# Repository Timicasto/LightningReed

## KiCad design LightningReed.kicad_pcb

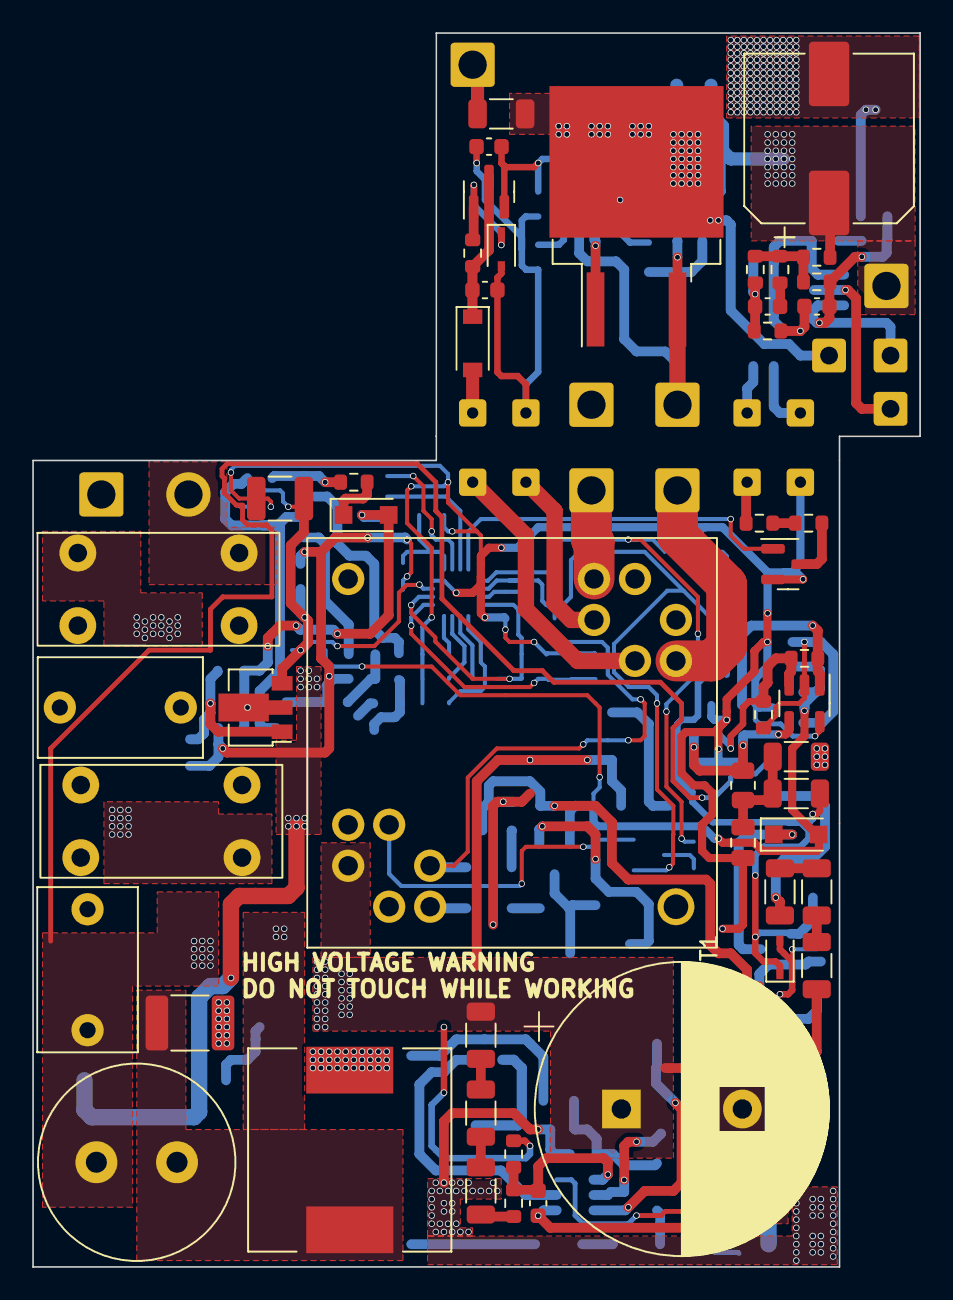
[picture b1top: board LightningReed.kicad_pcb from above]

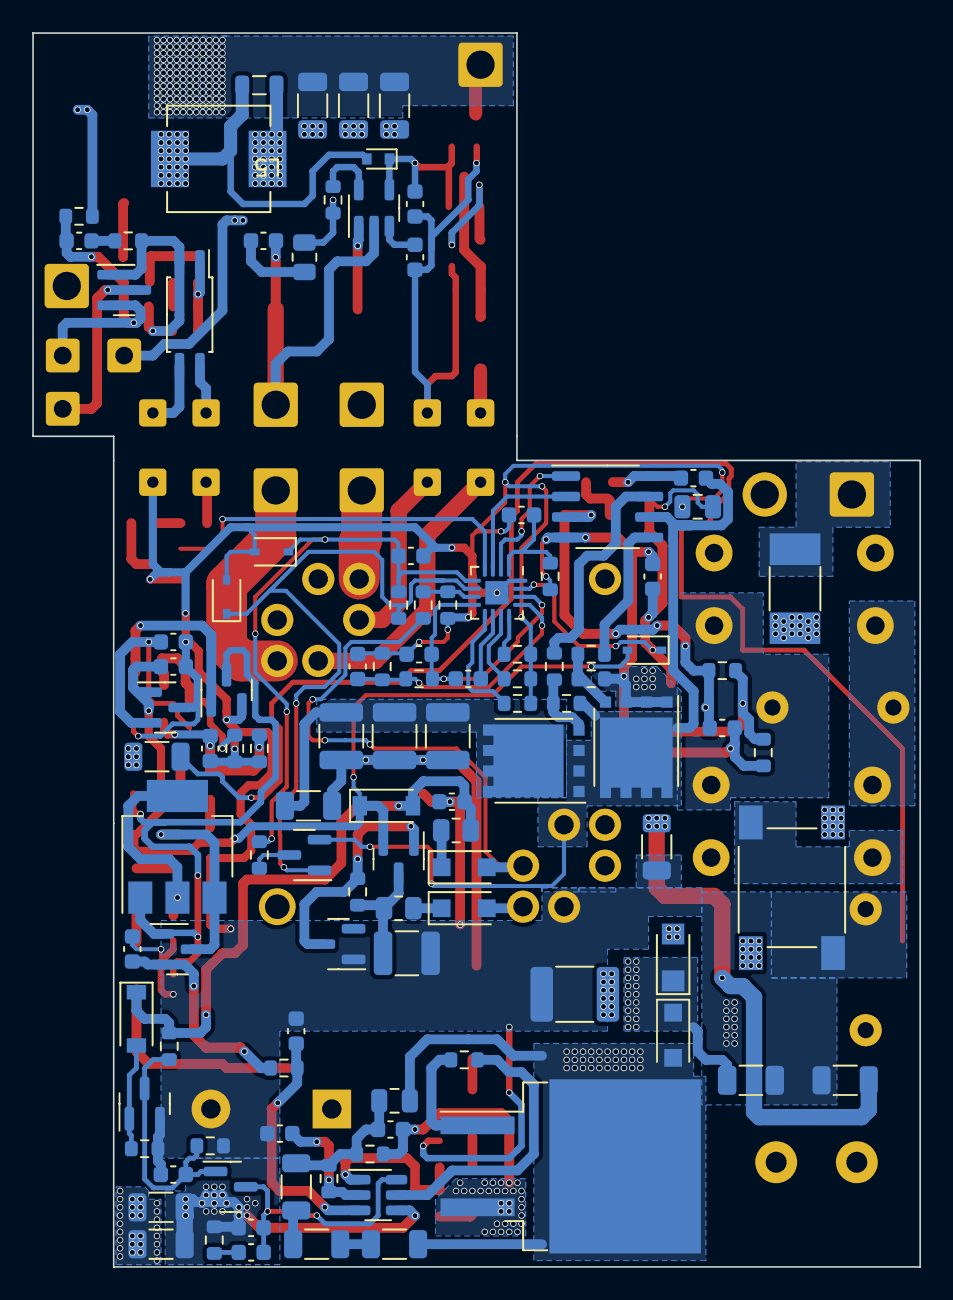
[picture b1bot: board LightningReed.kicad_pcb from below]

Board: 2 copper layers, 55.0 x 76.5 mm, 175 parts (108 on the bottom side), 102 nets.

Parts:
C1: 470nF; C_Rect_L10.0mm_W6.0mm_P7.50mm_MKS4
C2: 220nF; C_Rect_L10.0mm_W6.0mm_P7.50mm_MKS4
C3, C19: 470nF; C_1812_4532Metric
C4: 10pF; C_0805_2012Metric
C5: 3900pF; C_0603_1608Metric
C6, C11, C12, C13, C15, C25, C44, C45, C46: 1uF; C_0603_1608Metric
C7: 33nF; C_0603_1608Metric
C8, C14, C17, C31, C32, C38: 220pF; C_0603_1608Metric
C9: 2200pF; C_0603_1608Metric
C10: 68uF; CP_Radial_D18.0mm_P7.50mm
C16: 100nF; C_0805_2012Metric
C18: 100nF; C_1206_3216Metric
C20, C21, C22: 330nF; C_1210_3225Metric
C23: 47nF; C_0603_1608Metric
C24, C30: 100nF; C_0603_1608Metric
C26, C47: 2.2uF; C_0603_1608Metric
C27: 4.7uF; C_1210_3225Metric
C28: 4.7uF; C_0805_2012Metric
C29: 22uF; C_1210_3225Metric
C33: 33pF; C_0603_1608Metric
C34: 22pF; C_0603_1608Metric
C35: 4.7nF; C_0603_1608Metric
C36: 10nF; C_0603_1608Metric
C37: 3.3pF; C_0603_1608Metric
C39, C40, C41, C42: 33uF; C_1206_3216Metric
C43: 680uF; CP_Elec_10x10
D1: ES3JF; D_SMF
D2: MSB40M; UMSB
D3: ES2JW; D_SOD-123F
D4: BZT52C16S; D_SOD-323
D5: DSK16; D_SOD-123F
D6: BZT52C13; D_SOD-123
D7: U1J; D_SOD-123F
D8, D9: ES1JW; D_SOD-123F
D10: SD103AW; D_SOD-123
D11: BAS70WS; D_SOD-323
D12: BZX84C16; SOT-23
D13: MM3Z20; D_SOD-323
D14: MM3Z24; D_SOD-323
D15: RF081M2STR; D_SOD-123
D16: MM3Z10; D_SOD-323
D17: RFU02VSM8S; D_SOD-523
F1: JFC2410-1500TS; JFC2410
L1, L2: 5mH; CHOKE
L3: SDA0912-150uH-0.45; L_Radial_D12.0mm_P5.00mm_Fastron_11P
L4: 7447709471; L_12x12mm_H8mm
L5: 1uH; CKST0603
L6: 680nH; L_0805_2012Metric
P1: Conn_WallPlug; SolderWire-1sqmm_1x02_P5.4mm_D1.4mm_OD2.7mm
Q1: NCE65T180D; TO-263-2
Q2, Q4: 2N7002; SOT-23
Q3: 1N60G; SOT-223-3_TabPin2
Q5, Q6, Q11: 2N7002K; SOT-23
Q7, Q8: CMSA65R280Q; VSONP-8-1EP_5x6_P1.27mm
Q9: NCE0102; SOT-23
Q10: DMZ6005E; SOT-23
Q12: NCEP15T14D; TO-263-2
Q13: BSS123; SOT-23
R1, R31, R35, R54: 10; R_0603_1608Metric
R2, R3, R4, R10, R11, R12, R19, R20, R24: 3M24; R_1206_3216Metric
R5: 24K3; R_0603_1608Metric
R6, R7, R38, R39: 220m; R_1206_3216Metric
R8: 182K; R_0603_1608Metric
R9: 750; R_0603_1608Metric
R13, R44: 274K; R_0603_1608Metric
R14: 64k9; R_0603_1608Metric
R15: 2; R_0603_1608Metric
R16, R18, R28: 100K; R_0603_1608Metric
R17: 39K2; R_0603_1608Metric
R21, R22, R23: 1K; R_1206_3216Metric
R25: 3M16; R_0805_2012Metric
R26: 178K; R_0603_1608Metric
R27: 49K9; R_0603_1608Metric
R29, R32, R34, R56: 10K; R_0603_1608Metric
R30: 2M21; R_1206_3216Metric
R33: 24.9; R_0603_1608Metric
R36: 470; R_0603_1608Metric
R37: 3K24; R_0603_1608Metric
R40, R41: 1; R_0805_2012Metric
R42, R43, R58, R60: 150K; R_0603_1608Metric
R45, R46: 332K; R_0603_1608Metric
R47: 1K21; R_0603_1608Metric
R48: 1M; R_0603_1608Metric
R49: 121; R_0603_1608Metric
R50: 12K4; R_0603_1608Metric
R51, R63: 75K; R_0603_1608Metric
R52: 30K1; R_0603_1608Metric
R53: 432K; R_0603_1608Metric
R55: 562; R_0603_1608Metric
R57: 15K; R_0603_1608Metric
R59: 56K2; R_0603_1608Metric
R61: 22; R_0805_2012Metric
R62: 100; R_0603_1608Metric
T1: Transformer_2P_2S; RM10
TH1: 100K; R_0603_1608Metric
TP1: TestPoint_Alt; SolderWire-1sqmm_1x01_D1.4mm_OD2.7mm
TP2, TP3, TP4: TestPoint_Alt; SolderWire-0.5sqmm_1x01_D0.9mm_OD2.1mm
TP5, TP6, TP7, TP8: TestPoint; SolderWire-1sqmm_1x01_D1.4mm_OD2.7mm
TP9, TP10, TP11, TP12, TP13, TP14, TP15, TP16: TestPoint; SolderWire-0.15sqmm_1x01_D0.5mm_OD1.5mm
U1: UCC28056; SOT-23-6
U2: 78L05S; SOT-23
U3: LMC7111; SOT-23-5
U4: UCC28780; QFN-16-1EP_3x3mm_P0.5mm_EP1.45x1.45mm
U5: UCC27712; SO-8_3.9x4.9mm_P1.27mm
U6: LM317LCPK; SOT-89-3
U7: FODM8801A; SOP-4_4.4x2.6mm_P1.27mm
U8: TL431DBZ; SOT-23
U9: UCC24612-1DBV; SOT-23-5

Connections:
/5V_LDO: C13.1, R16.2, U2.1 (OUT), U3.2 (V+)
/AC_SENSE: C14.1, R25.1, R26.2, U3.4 (-)
/BROWN_OUT: D4.1 (K), Q2.3 (D), Q3.1 (G), Q4.1 (G), R24.1
/BUR: C32.2, R45.1, R46.2, U4.13 (BUR)
/COMP: C6.2, C7.2, Q5.3 (D), U1.6 (COMP)
/CS: C33.2, R47.2, U4.1 (CS)
/CTL: C36.2, C37.2, R58.1, R60.2, TP4.1, U8.2 (REF)
/FB: C31.1, U4.10 (FB)
/PWMH: U4.3 (PWMH), U5.2 (HI)
/PWML: U4.2 (PWML), U5.1 (LI)
/RUN: Q11.1 (G), U4.4 (RUN)
/VAUX: D15.2 (A), TP12.1
/VCC_PFC: C15.1, Q4.2 (S), R15.2
/VDD1: C27.2, Q9.3 (D), R41.2, R42.2
/VDD2: C26.2, D6.1 (K), D10.2 (A), R27.2, R40.2
/VDD3: C12.1, D5.2 (A), D10.1 (K), D11.2 (A), Q9.2 (S), U2.3 (IN)
/VREF: C30.1, C31.2, R45.2, U4.8 (SET), U4.14 (REF)
/VSV: D8.2 (A), R51.1, T1.5 (SD)
/VSW: C23.2, Q7.1 (S), Q8.3 (D), Q10.2 (D), R32.2, T1.7 (AA), U5.6 (HS)
GNDPWR: C2.2, C3.2, C7.1, C8.2, C9.2, C10.2, C11.2, C12.2, C13.2, C14.2, C15.2, C16.2, C17.2, C18.2, C19.2, C26.1, C27.1, C28.1, C29.1, C30.2, C32.1, C33.1, C34.2, D2.2 (-), D4.2 (A), D12.1 (A), D13.2 (A), D14.2 (A), Q2.2 (S), Q5.2 (S), Q6.2 (S), Q11.2 (S), R6.1, R7.1, R8.1, R14.1, R17.1, R26.1, R28.1, R29.1, R38.1, R39.1, R43.1, R44.1, R46.1, R50.1, T1.1 (SD), TH1.1, TP14.1, U1.4 (GND), U2.2 (GND), U3.5 (V-), U4.16 (GND), U4.17 (GND)
GNDS: C39.2, C40.2, C41.2, C42.2, C43.2, R60.1, TP3.1, TP7.1, U8.3 (A)
HT: C2.1, D2.1 (+), L3.1, R19.2
LINE: C43.1, D17.2 (A), L5.2, L6.2, R54.2, TP1.1
unnamed: C1.1, L1.2, L2.1
unnamed: C1.2, L1.4, L2.3
unnamed: C4.2, C5.1, R4.1, R5.2, R9.1
unnamed: C6.1, R8.2
unnamed: C16.1, R20.1, R24.2, R25.2
unnamed: C35.1, R55.1
unnamed: C35.2, R56.1, R57.2, U7.1
unnamed: C36.1, R59.1
unnamed: C38.2, R61.2
unnamed: C3.1, D1.2 (A), L3.2, L4.2
unnamed: D2.3, L2.4
unnamed: D2.4, L2.2
unnamed: C4.1, D3.2 (A), L4.1, Q1.2 (D), R2.2
unnamed: D5.1 (K), Q3.3 (S), Q4.3 (D)
unnamed: D6.2 (A), Q6.1 (G), R29.2
unnamed: C25.1, D7.2 (A), R36.1, U5.3 (VDD), U6.2 (VO)
unnamed: D7.1 (K), R35.2
unnamed: D8.1 (K), R40.1
unnamed: D9.2 (A), T1.2 (SC)
unnamed: D9.1 (K), R41.1
unnamed: D12.3 (K), Q9.1 (G), R42.1
unnamed: C34.1, D13.1 (K), R48.1, R49.1, U4.5 (SWS)
unnamed: D14.1 (K), Q10.1 (G), R48.2, U4.6 (HVG)
unnamed: C44.2, D15.1 (K), Q13.3 (D), R63.2
unnamed: D16.1 (K), Q13.1 (G), R63.1
unnamed: C45.2, C46.1, D17.1 (K), Q13.2 (S), U9.4 (VDD)
unnamed: F1.2, L1.1
unnamed: L1.3, P1.2 (AC_N)
unnamed: F1.1, P1.1 (AC_P)
unnamed: Q1.1 (G), R1.2
unnamed: C5.2, Q1.3 (S), R5.1, R6.2, R7.2
unnamed: Q2.1 (G), R18.1, U3.1
unnamed: Q3.2 (D), R23.2
unnamed: C17.1, Q5.1 (G), Q6.3 (D), R27.1, R28.2
unnamed: C20.2, C21.2, C22.2, Q7.3 (D), R30.1
unnamed: Q7.2 (G), R31.1, R32.1
unnamed: Q8.2 (G), R33.1, R34.1
unnamed: C24.2, C25.2, Q8.1 (S), R34.2, R37.2, R38.2, R39.2, R47.1, U5.4 (COM)
unnamed: Q10.3 (S), R49.2
unnamed: Q11.3 (D), R53.2
unnamed: Q12.1 (G), U9.1 (VG)
unnamed: C38.1, Q12.3 (S), TP5.1, U9.2 (VS)
unnamed: R2.1, R3.2
unnamed: R3.1, R4.2
unnamed: R10.1, R11.2
unnamed: R11.1, R12.2
unnamed: R12.1, R13.2
unnamed: R19.1, R20.2
unnamed: R21.2, R22.1
unnamed: R22.2, R23.1
unnamed: R52.1, TP13.1
unnamed: R52.2, R53.1
unnamed: R54.1, R55.2, R56.2, R58.2
unnamed: T1.9 (SA), TP6.1
unnamed: T1.13 (SB), TP8.1
unnamed: T1.8 (SC), TP9.1
unnamed: T1.10 (SD), TP10.1
unnamed: TP15.1, U7.4
unnamed: TP16.1, U7.3
unnamed: R1.1, U1.5 (DRV)
unnamed: C11.1, R15.1, U1.3 (VCC)
unnamed: C9.1, R13.1, R14.2, U1.1 (VOSNS)
unnamed: C8.1, R9.2, U1.2 (ZCD)
unnamed: R16.1, R17.2, R18.2, U3.3 (+)
unnamed: TH1.2, U4.9 (NTC)
unnamed: R43.2, U4.12 (RDM)
unnamed: R44.2, U4.11 (RTZ)
unnamed: R50.2, R51.2, U4.7 (VS)
unnamed: C23.1, R35.1, U5.8 (HB)
unnamed: R31.2, U5.7 (HO)
unnamed: R33.2, U5.5 (LO)
unnamed: R36.2, R37.1, U6.1 (ADJ)
unnamed: C37.1, R57.1, R59.2, U7.2, U8.1 (K)
unnamed: C47.2, U9.3 (REG)
unnamed: R62.2, U9.5 (VD)
VCOM: C39.1, C40.1, C41.1, C42.1, L5.1, L6.1, Q12.2 (D), R61.1, R62.1, TP2.1
VDC: C10.1, C18.1, C19.1, C20.1, C21.1, C22.1, D1.1 (K), D3.1 (K), R10.2, R21.1, R30.2, T1.4 (AB)
VDD: C24.1, C28.2, C29.2, D11.1 (K), U4.15 (VDD), U6.3 (VI)
VS: C44.1, C45.1, C46.2, C47.1, D16.2 (A), TP11.1

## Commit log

2023-05-28 Init commit
2023-05-30 PFC choke
2023-05-30 PFC Controller symbol
2023-06-01 File Sync
2023-06-02 VCCPFC
2023-06-02 brown out circuit
2023-06-03 PFC complete
2023-06-04 Flyback controller
2023-06-08 Transformer
2023-06-08 HB Driver
2023-06-09 Flyback Controller VDDBias Power
2023-06-10 Controller Out
2023-06-10 Complete Schematic
2023-06-12 C Footprint
2023-06-12 Footprints
2023-06-13 Complete footprints
2023-06-17 Finish footprints
2023-06-17 routing 1/?
2023-06-18 PFC Layout
2023-06-18 SR layout
2023-06-19 Flyback controller left - layout
2023-06-20 Controller 50%
2023-06-21 Finish
